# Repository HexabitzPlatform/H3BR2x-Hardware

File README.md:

# H3BR2x-Hardware
Hexabitz 2-Digit 7-Segment display Module Hardware Design

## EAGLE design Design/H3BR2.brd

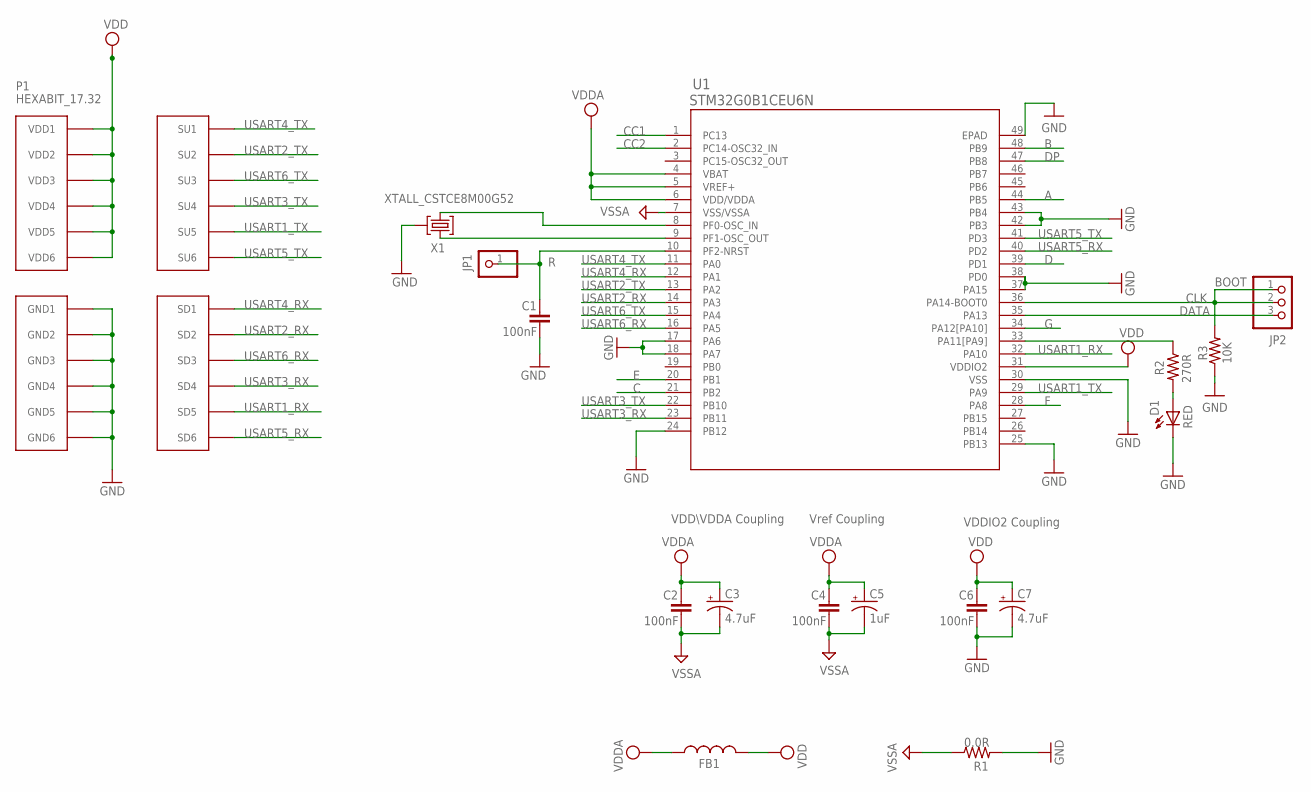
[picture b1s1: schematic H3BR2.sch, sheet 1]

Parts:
C1, C2, C4, C6: 100nF; C-0402
C3, C7: 4.7uF; C-0805-POL
C5: 1uF; C-0805-POL
D1: RED; VLMS1300-GS08; MPN VLMS1300-GS08
FB1: FB-0603
JP1: R; 1X01
JP2: PINHD-1X3; 1X03
P1: HEXABIT_17.32
R1: 0.0R; R-0402
R2: 270R; R-0603
R3: 10K; R-0402
U1: STM32G0B1CEU6N; QFN_B1CEU6_STM-L
X1: XTALL_CSTCE8M00G52

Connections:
A: U1.44 (PB5); also elsewhere on the board
B: U1.48 (PB9); also elsewhere on the board
C: U1.21 (PB2); also elsewhere on the board
CC1: U1.1 (PC13); also elsewhere on the board
CC2: U1.2 (PC14-OSC32_IN); also elsewhere on the board
CLK: JP2.1, JP2.2, R3.2, U1.36 (PA14-BOOT0)
D: U1.39 (PD1); also elsewhere on the board
DATA: JP2.3, U1.35 (PA13)
DP: U1.47 (PB8); also elsewhere on the board
E: U1.20 (PB1); also elsewhere on the board
F: U1.28 (PA8); also elsewhere on the board
G: U1.34 (PA12[PA10]); also elsewhere on the board
GND: C1.2, C6.2, C7.2 (-), D1.C, P1.PAD_PD7 (GND1), P1.PAD_PD8 (GND2), P1.PAD_PD9 (GND3), P1.PAD_PD10 (GND4), P1.PAD_PD11 (GND5), P1.PAD_PD12 (GND6), R1.2, R3.1, U1.17 (PA6), U1.18 (PA7), U1.24 (PB12), U1.25 (PB13), U1.30 (VSS), U1.37 (PA15), U1.38 (PD0), U1.42 (PB3), U1.43 (PB4), U1.49 (EPAD), X1.P$2 (2); also elsewhere on the board
unnamed: D1.A, R2.2
unnamed: R2.1, U1.33 (PA11[PA9])
unnamed: U1.9 (PF1-OSC_OUT), X1.P$1 (1)
unnamed: U1.8 (PF0-OSC_IN), X1.P$3 (3)
unnamed: C1.1, JP1.1, U1.10 (PF2-NRST)
USART1_RX: P1.PAD_PD5 (SD5), U1.32 (PA10)
USART1_TX: P1.PAD_PU5 (SU5), U1.29 (PA9)
USART2_RX: P1.PAD_PD2 (SD2), U1.14 (PA3)
USART2_TX: P1.PAD_PU2 (SU2), U1.13 (PA2)
USART3_RX: P1.PAD_PD4 (SD4), U1.23 (PB11)
USART3_TX: P1.PAD_PU4 (SU4), U1.22 (PB10)
USART4_RX: P1.PAD_PD1 (SD1), U1.12 (PA1)
USART4_TX: P1.PAD_PU1 (SU1), U1.11 (PA0)
USART5_RX: P1.PAD_PD6 (SD6), U1.40 (PD2)
USART5_TX: P1.PAD_PU6 (SU6), U1.41 (PD3)
USART6_RX: P1.PAD_PD3 (SD3), U1.16 (PA5)
USART6_TX: P1.PAD_PU3 (SU3), U1.15 (PA4)
VDD: C6.1, C7.1 (+), FB1.2, P1.PAD_PU7 (VDD1), P1.PAD_PU8 (VDD2), P1.PAD_PU9 (VDD3), P1.PAD_PU10 (VDD4), P1.PAD_PU11 (VDD5), P1.PAD_PU12 (VDD6), U1.31 (VDDIO2); also elsewhere on the board
VDDA: C2.1, C3.1 (+), C4.1, C5.1 (+), FB1.1, U1.4 (VBAT), U1.5 (VREF+), U1.6 (VDD/VDDA)
VSSA: C2.2, C3.2 (-), C4.2, C5.2 (-), R1.1, U1.7 (VSS/VSSA)

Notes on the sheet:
Vref Coupling
VDDIO2 Coupling
VDD\VDDA Coupling
BOOT

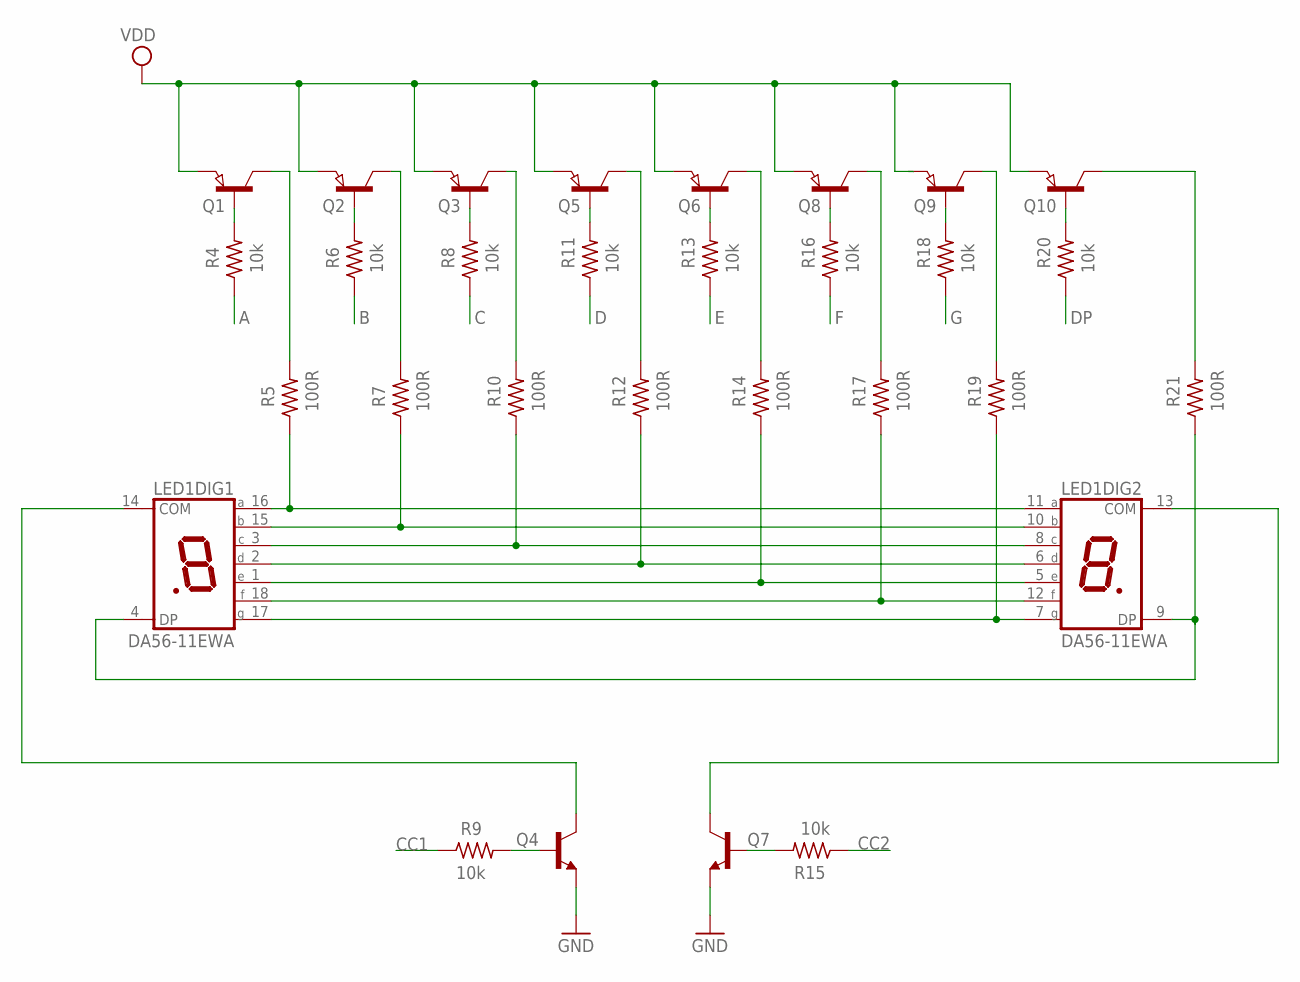
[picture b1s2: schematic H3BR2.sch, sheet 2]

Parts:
LED1: DA56-11EWA; DA56; MPN LTD-6940HR
Q1, Q2, Q3, Q5, Q6, Q8, Q9, Q10: SEMICON-SMD-IPC_PNP-TRANSISTOR_SOT23; SEMICON-SMD-IPC_SOT23
Q4, Q7: MMBT3904LT1
R4, R6, R8, R9, R11, R13, R15, R16, R18, R20: 10k; R-0402
R5, R7, R10, R12, R14, R17, R19, R21: 100R; R-0402

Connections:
A: R4.1; also elsewhere on the board
B: R6.1; also elsewhere on the board
C: R8.1; also elsewhere on the board
CC1: R9.1; also elsewhere on the board
CC2: R15.1; also elsewhere on the board
D: R11.1; also elsewhere on the board
DP: R20.1; also elsewhere on the board
E: R13.1; also elsewhere on the board
F: R16.1; also elsewhere on the board
G: R18.1; also elsewhere on the board
GND: Q4.2 (E), Q7.2 (E); also elsewhere on the board
unnamed: LED1.10 (B), LED1.15 (B), R7.1
unnamed: Q1.1 (B), R4.2
unnamed: Q2.1 (B), R6.2
unnamed: Q9.3 (C), R19.2
unnamed: Q8.3 (C), R17.2
unnamed: Q6.3 (C), R14.2
unnamed: Q5.3 (C), R12.2
unnamed: Q3.3 (C), R10.2
unnamed: Q2.3 (C), R7.2
unnamed: Q1.3 (C), R5.2
unnamed: Q3.1 (B), R8.2
unnamed: Q5.1 (B), R11.2
unnamed: Q6.1 (B), R13.2
unnamed: Q8.1 (B), R16.2
unnamed: Q9.1 (B), R18.2
unnamed: Q10.1 (B), R20.2
unnamed: LED1.11 (A), LED1.16 (A), R5.1
unnamed: LED1.4 (DP), LED1.9 (DP), R21.1
unnamed: LED1.3 (C), LED1.8 (C), R10.1
unnamed: LED1.2 (D), LED1.6 (D), R12.1
unnamed: LED1.1 (E), LED1.5 (E), R14.1
unnamed: LED1.12 (F), LED1.18 (F), R17.1
unnamed: LED1.7 (G), LED1.17 (G), R19.1
unnamed: LED1.14 (COM), Q4.3 (C)
unnamed: LED1.13 (COM), Q7.3 (C)
unnamed: Q7.1 (B), R15.2
unnamed: Q4.1 (B), R9.2
unnamed: Q10.3 (C), R21.2
VDD: Q1.2 (E), Q2.2 (E), Q3.2 (E), Q5.2 (E), Q6.2 (E), Q8.2 (E), Q9.2 (E), Q10.2 (E); also elsewhere on the board

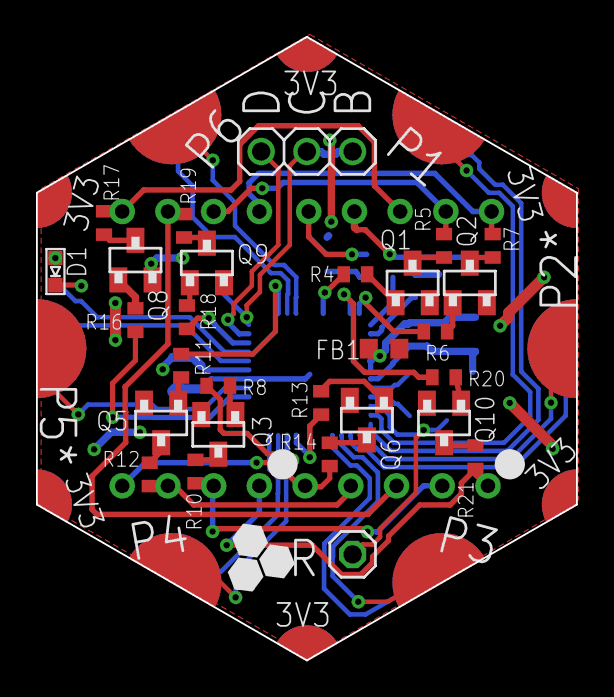
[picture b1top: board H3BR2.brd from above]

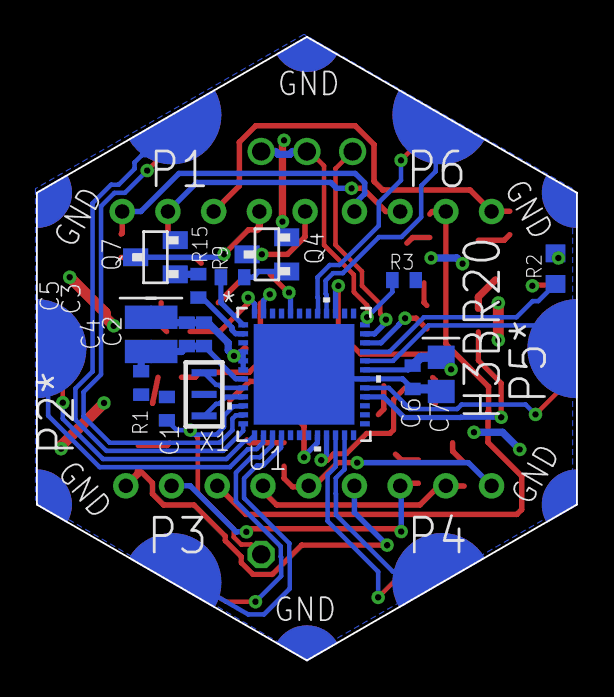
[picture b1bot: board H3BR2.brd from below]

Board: 2 copper layers, 30.0 x 34.6 mm, 46 parts (16 on the bottom side), 61 nets.

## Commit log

2022-12-28 The first version of the module with stm32g0 MCU
2023-02-13 -Correcting some documentaion issues
2023-03-23 fix bom
2024-02-13 -Fixing Documentation Issues

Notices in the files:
parts and their libraries:
HEXABITZ_ICs: COPYRIGHT: Copyright (C) 2022 Ultra Librarian. All rights reserved.
